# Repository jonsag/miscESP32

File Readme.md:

# miscESP32

## ESP32-CAM Programmer

[ESP32-Cam Programmer@instructables](https://www.instructables.com/ESP32-Cam-Programmer/)  
By [nextinnovator](https://www.instructables.com/member/nextinnovator/)  

## ESP32-CAM web server

esp32-cam-webserver-pio is built on  
[esp32-cam-webserver](https://github.com/easytarget/esp32-cam-webserver/)  
and is the one working best  

CameraWebServer is from Arduino IDE examples

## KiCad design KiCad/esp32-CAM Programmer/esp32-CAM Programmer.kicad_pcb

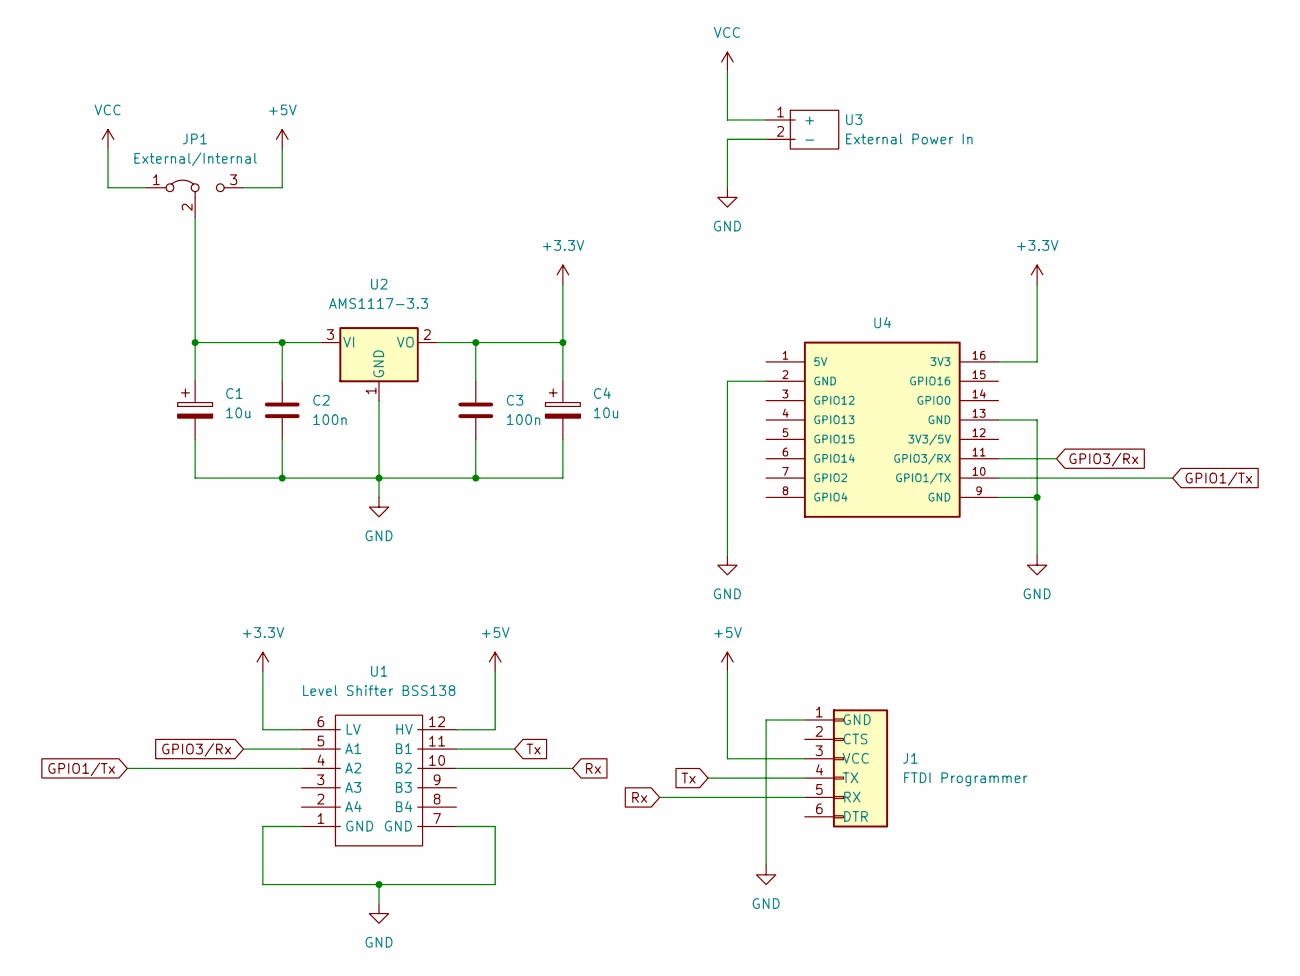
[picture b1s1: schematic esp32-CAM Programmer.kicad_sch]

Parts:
C1, C4: 10u; CP_Radial_D5.0mm_P2.00mm_larger
C2, C3: 100n; C_Disc_D3.0mm_W1.6mm_P2.50mm_larg
J1: FTDI Programmer; 6-pin FTDI Programmer PinSocket large
JP1: External/Internal; Jumper_1x03_P2.54mm_large
U1: Level Shifter BSS138; 4-channel_I2C_level_shifter_BSS138_large
U2: AMS1117-3.3; SOT-223-3_TabPin2
U3: External Power In; 2-pin_power_input_header_larger_pads
U4: ESP32-CAM

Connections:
+3.3V: C3.1, C4.1, U1.6 (LV), U2.2 (VO), U4.16 (3V3)
+5V: J1.3 (VCC), JP1.3 (B), U1.12 (HV)
GND: C1.2, C2.2, C3.2, C4.2, J1.1 (GND), U1.1 (GND), U1.7 (GND), U2.1 (GND), U3.2 (-), U4.2 (GND), U4.9 (GND), U4.13 (GND)
GPIO1/Tx: U1.4 (A2), U4.10 (GPIO1/TX)
GPIO3/Rx: U1.5 (A1), U4.11 (GPIO3/RX)
unnamed: C1.1, C2.1, JP1.2 (C), U2.3 (VI)
Rx: J1.5 (RX), U1.10 (B2)
Tx: J1.4 (TX), U1.11 (B1)
VCC: JP1.1 (A), U3.1 (+)

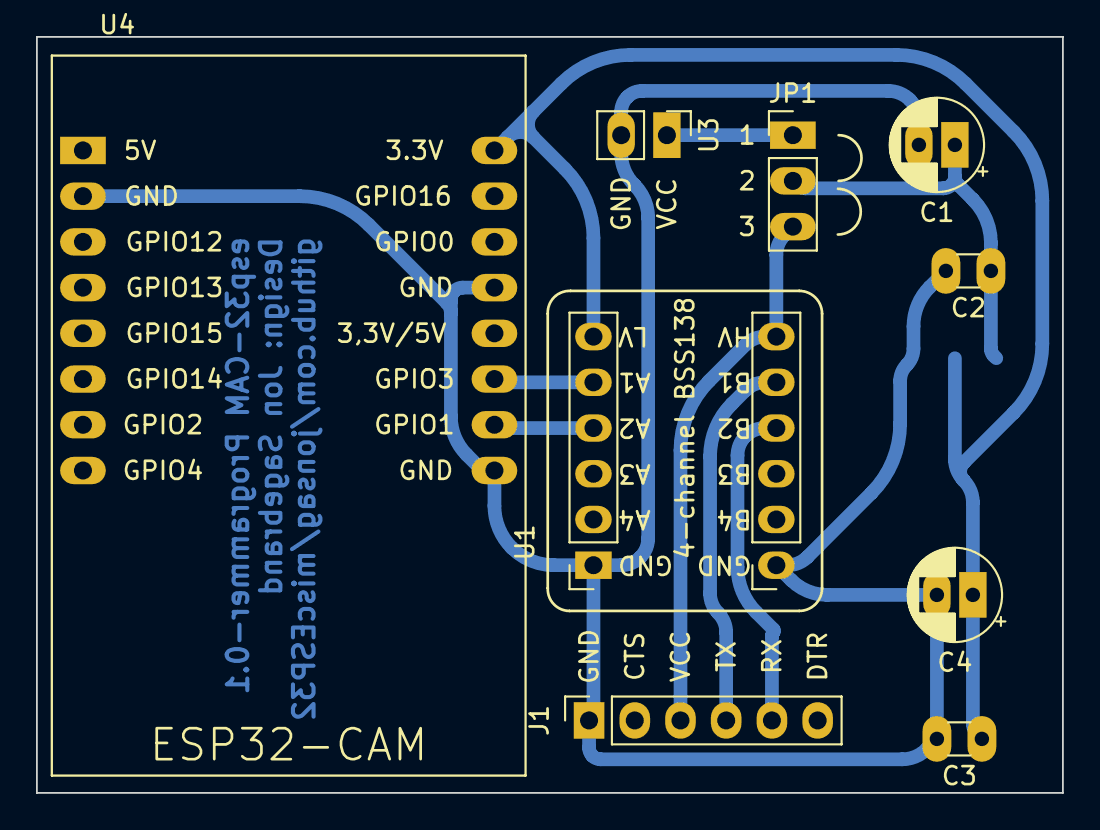
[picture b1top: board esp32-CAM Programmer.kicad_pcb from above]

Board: 2 copper layers, 57.0 x 42.0 mm, 10 parts (1 on the bottom side), 9 nets.

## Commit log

2022-12-13 cam web servers
2022-12-13 moved README
2025-02-09 workspace
2025-02-17 moves
2025-02-18 gitignore secrets
